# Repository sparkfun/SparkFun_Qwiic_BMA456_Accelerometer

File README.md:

---------------------------------------------------------

The [SparkFun Triple Axis Accelerometer Breakout - BMA456 (Qwiic)](https://www.sparkfun.com/sparkfun-triple-axis-accelerometer-breakout-bma456-qwiic.html) is a compact, plug-and-play motion sensing board built around the Bosch Sensortec BMA456, a 16-bit digital triaxial accelerometer with an on-chip feature engine for motion-triggered interrupts. Connect via the Qwiic connector or the PTH header and start reading acceleration over I2C in minutes, no external components required.

The BMA456 offers user-selectable measurement ranges of ±2g, ±4g, ±8g, and ±16g, low-pass filter bandwidths from 684Hz down to under 8Hz, and output data readout up to 1.6kHz. A 1kb on-chip FIFO buffers samples so your microcontroller does not have to poll continuously, and two configurable interrupt pins (INT1 and INT2) let the sensor wake your system only when something actually happens. The on-chip feature engine handles motion-triggered events in hardware, including any-motion and no-motion detection, single and double tap, tilt, orientation, and step counting, freeing your processor to sleep the rest of the time.

Designed for our [Qwiic ecosystem](https://www.sparkfun.com/qwiic), this 1" × 1" board plugs straight into any Qwiic-enabled microcontroller. An address jumper selects between I2C addresses 0x18 and 0x19 so you can put two of these on the same bus, and the PTH header breaks out the full SPI interface alongside I2C for applications that need a faster or dedicated connection. A power LED confirms operation at a glance, and the four mounting holes make permanent installation straightforward. Whether you are building a wearable activity tracker, adding tap-to-wake to a battery powered project, measuring tilt angle, or logging vibration and orientation, the BMA456 delivers low-power motion sensing in a breadboard-friendly package.

## Features

* Bosch Sensortec BMA456 16-bit triaxial accelerometer
* Selectable ranges: ±2g / ±4g / ±8g / ±16g
* Output data readout up to 1.6kHz
* Low-pass filter bandwidths from 684Hz to under 8Hz
* 1kb on-chip FIFO
* On-chip feature engine: any-motion, no-motion, single and double tap, tilt, orientation, step counter
* Two configurable interrupt pins (INT1, INT2)
* I2C and SPI (4-wire and 3-wire) interfaces
* Selectable I2C addresses: 0x18 (default) / 0x19
* 3.3V operation via Qwiic, IO supply range 1.2V to 3.6V
* Ultra-low power operation
* Two Qwiic connectors and a 0.1" PTH header
* 1.0" × 1.0" with four mounting holes

## Repository Contents

* **/docs** - Documentation files for GitHub pages
* **/Documents** - Datasheets, additional product information
* **/Hardware** - KiCad design files (.kicad_sch, .kicad_pcb)
* **/Production** - Production panel files

## Documentation

* **[Library](https://github.com/sparkfun/SparkFun_BMA456_Arduino_Library)** - Arduino library for the SparkFun Triple Axis Accelerometer Breakout - BMA456 (Qwiic).
* **[Hookup Guide](https://docs.sparkfun.com/SparkFun_Triple_Axis_Accelerometer_Breakout_BMA456/)** - Basic hookup guide for the SparkFun Triple Axis Accelerometer Breakout - BMA456 (Qwiic).

## Product Versions

* **[SEN-32097](https://www.sparkfun.com/sparkfun-triple-axis-accelerometer-breakout-bma456-qwiic.html)** - Initial release of the SparkFun Triple Axis Accelerometer Breakout - BMA456 (Qwiic).

## License Information

This product is _**open source**_!

Please review the LICENSE.md file for license information.

If you have any questions or concerns about licensing, please contact technical support on our [SparkFun forums](https://forum.sparkfun.com/viewforum.php?f=152).

Distributed as-is; no warranty is given.

_- Your friends at SparkFun._

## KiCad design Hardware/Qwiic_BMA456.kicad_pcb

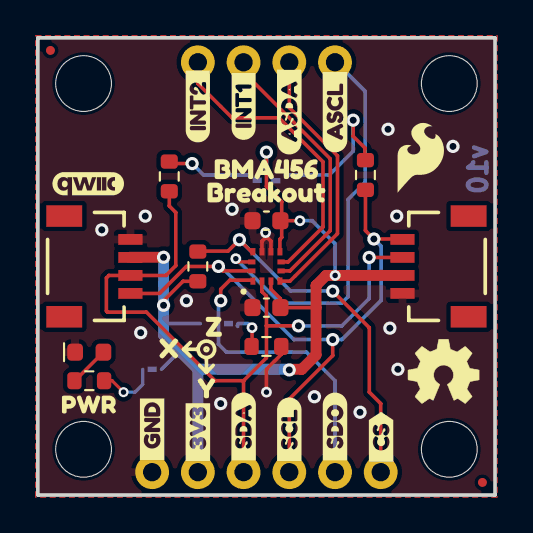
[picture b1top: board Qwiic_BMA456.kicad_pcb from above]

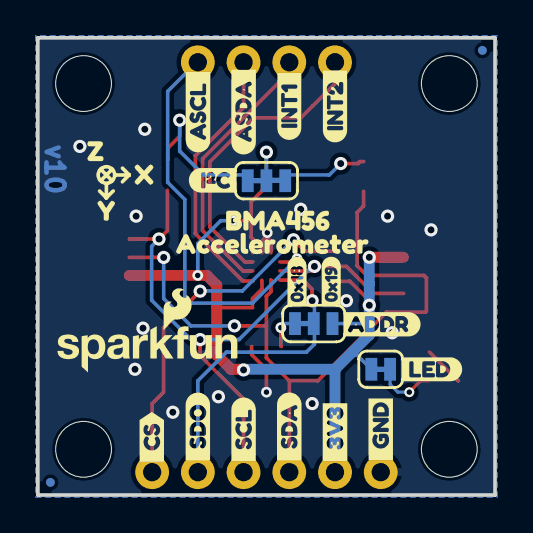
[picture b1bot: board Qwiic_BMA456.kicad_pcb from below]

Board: 2 copper layers, 25.4 x 25.4 mm, 61 parts (25 on the bottom side), 15 nets.

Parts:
C1, C4: 0.1uF; C_0603_1608Metric
D1: Red; LED_0603_1608Metric_Red
FID1, FID2, FID3, FID4: Fiducial_0.5mm; Fiducial_0.5mm_Mask1mm
J0: LED; Jumper_2_NC_Trace
J1: Conn_01x04; 1x04_P2.54mm
J2, J4: Qwiic_RA; JST_1x04_P1.0mm_Horizontal_SMD
J3: I²C; Jumper_3_NC-2_Trace
J5: Conn_01x06; 1x06_P2.54mm
J6: ADDR; Jumper_3_NC-1_Trace
R1, R2, R3, R4, R7: 4.7k; R_0603_1608Metric
Ref**: Val**; OSHW_Logo_4mm
ST3, ST4, ST7, ST8: Standoff
U1: BMA456; LGA-12_2x2mm
kibuzzard-6A8DBB71: G***; kibuzzard-6A8DBB71
kibuzzard-6A8DBB79: G***; kibuzzard-6A8DBB79
kibuzzard-6A8DBBAF, kibuzzard-6A8DBBAF#2: G***; kibuzzard-6A8DBBAF
kibuzzard-6A8DBBBE, kibuzzard-6A8DBBBE#2: G***; kibuzzard-6A8DBBBE
kibuzzard-6A8DBBCD, kibuzzard-6A8DBBCD#2: G***; kibuzzard-6A8DBBCD
kibuzzard-6A8DBBD9, kibuzzard-6A8DBBD9#2: G***; kibuzzard-6A8DBBD9
kibuzzard-6A8DC94F: G***; kibuzzard-6A8DC94F
kibuzzard-6A8DC959: G***; kibuzzard-6A8DC959
kibuzzard-6A84B2F6: G***; kibuzzard-6A84B2F6
kibuzzard-6A84B31F: G***; kibuzzard-6A84B31F
kibuzzard-6A848A2E, kibuzzard-6A848A2E#2: G***; kibuzzard-6A848A2E
kibuzzard-6A848A36, kibuzzard-6A848A36#2: G***; kibuzzard-6A848A36
kibuzzard-6A848AC1: G***; kibuzzard-6A848AC1
kibuzzard-6A848B8C: G***; kibuzzard-6A848B8C
kibuzzard-6A848CE4: G***; kibuzzard-6A848CE4
kibuzzard-6A848CEC: G***; kibuzzard-6A848CEC
kibuzzard-6A848D2C: G***; kibuzzard-6A848D2C
kibuzzard-6A848D3D: G***; kibuzzard-6A848D3D
kibuzzard-6A8489CE, kibuzzard-6A8489CE#2: G***; kibuzzard-6A8489CE
kibuzzard-689A642E: G***; kibuzzard-689A642E
kibuzzard-689A6711, kibuzzard-689A6711#2: G***; kibuzzard-689A6711
kibuzzard-689A6718, kibuzzard-689A6718#2: G***; kibuzzard-689A6718
kibuzzard-689A6721, kibuzzard-689A6721#2: G***; kibuzzard-689A6721
kibuzzard-689A6728, kibuzzard-689A6728#2: G***; kibuzzard-689A6728
kibuzzard-689A6796: G***; kibuzzard-689A6796

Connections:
3.3V: C1.1, C4.1, J0.2 (B), J2.2, J3.2 (B), J4.2, J5.2, J6.3 (C), R2.2, U1.3 (VDDIO), U1.7 (VDD)
ASCL: J1.1, U1.11 (ASCL)
ASDA: J1.2, U1.4 (ASDA)
GND: C1.2, C4.2, D1.1 (K), J2.1, J4.1, J5.1, R4.1, U1.8 (GND), U1.9 (GND)
INT1: J1.3, U1.5 (INT1)
INT2: J1.4, U1.6 (INT2)
unnamed: D1.2 (A), R3.1
unnamed: J0.1 (A), R3.2
unnamed: J3.1 (A), R7.2
unnamed: J3.3 (C), R1.2
unnamed: J6.1 (A), R4.2
SCX: J2.4, J4.4, J5.4, R7.1, U1.12 (SCX)
SDO: J5.5, J6.2 (B), U1.1 (SDO)
SDX: J2.3, J4.3, J5.3, R1.1, U1.2 (SDX)
~CS: J5.6, R2.1, U1.10 (~CS)

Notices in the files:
Hardware/Qwiic_BMA456.kicad_pcb:
Released under the Creative Commons Attribution Share-Alike 4.0 License
https://creativecommons.org/licenses/by-sa/4.0
